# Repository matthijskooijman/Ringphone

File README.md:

Vintage phone audio player
==========================
This is the Ringphone project, a device that allows using old (mechanical
ring) phones to be used as a random audio player.

Repo status: Design is completely published, documentation is not
complete yet (mostly casing and firmware is lacking, harware is
documented well). Case design might not work as-is, but need some
changes to work with the latest boxes.py.

This project was created to facilitate the "Onze Kast" ("Our Cabinet")
project, which is a cabinet created by and for demented elderly people
with all kinds of things to explore and experience. In this cabinet,
there is an old bakelite phone that rings when someone approaches and
plays random audio samples when picked up. This repository documents the
design of this phone and contains all the needed source code and design
files to build it.

[More images...](./Images)

This project consists of three parts:
 - The electronics to connect to the telephone and detect motion.
 - The software to control everything.
 - A lasercut wooden case to house the electronics.

The sources and design files for these parts can be found in the `PCB`,
`RingPhoneSketch` and `Case` directories respectively. The `Data`
directory contains a template for the contents of the SD card.

A PDF version of the schematic, along with gerbers, board views and
other generated files for released board versions can be found under the
releases on the Github page.

This project uses an unmodified phone, connecting to it using the two
wires that normally connect to the telephone line (in essence, the
electronics emulate a telephone line). In theory it should be able to
work with any analog landline phone, though I have only tested it with
Dutch rotary dial phones from the sixties (and since the voltage and
current capability are not as high as true landlines, some phones might
not work).

Features
--------
Electronically, this project supports:
 - Making the phone ring.
 - Making the phone play a sound (through its regular earpiece).
 - Reading the rotary dial (this is supported electronically, but not by
   the software yet).
 - Detecting motion (using a standard motion detector module).

Receiving audio from the microphone is not supported at all.

The software supports:
 - Ringing the phone when motion is detected (with a fixed cooldown to
   not keep ringing all the time while motion is detected).
 - Playing a random sound whenever the phone is taken off-hook (also
   when it was not ringing).
 - Playing an "end of conversation" tone when the audio file completes
   playing.
 - Playing a new random sound whenever the rotary dial is used (this
   happens automatically, since using the rotary dial looks like putting
   the phone on-hook again).

Sketch
------
This sketch includes a copy of the
[AudioZero](https://github.com/arduino-libraries/AudioZero/) library,
modified to allow playing an audio file in the background. I considered
doing this properly (e.g. create a pull request for the library, maybe
use DMA for extra efficiency, etc.), but then it would probably be
better to add DAC out support to the
[ArduinoSound](https://github.com/arduino-libraries/ArduinoSound)
library instead (which was a bit more work than I was willing to invest
now).

Adding audio samples
--------------------
To add audio samples, they first must be encoded properly. The AudioZero
library is rather picky with the format and only understands 8-bit
unsigned 44.1kHz mono raw PCM files. This means the file just contains
the raw audio samples concatenated, without any header or other
accompanying information. Each sample is simply an 8-bit unsigned
integer. Note that this is even more raw than `.wav` file, which
typically have a header that describes the sample format in front of the
raw samples. This means that normal audioplayers cannot actually play
these raw PCM files, since they have no idea what format the samples are
in.

To encode these files, you can use Audacity. After loading a file, make
sure it is mono and has 44.1kHz sampling rate, then export it through
"File" -> "Export" -> "Export Audio..." and choose for "Other
uncompressed files" and then "Header: RAW (header-less)" and "Encoding:
Unsigned 8-bit PCM". Alternatively, you can convert to `.sou` files
using [this website](https://convertio.co/nl/sou-converter), but you
probably need to convert to 44.1Khz mono beforehand.

Once encoded, adding them is rather easy: Just dump the files onto the
μSD card. Make sure to use a `.raw` or `.sou` extension and to put the
files in the root (i.e. not in a subdirectory) of the μSD card.

Special sample file
-------------------
On the SD-card there should be a directory called `special` containing a
single file called `end.raw`. This is a sample (encoded as above), which
is played once after a normal sample has finished playing.

Electronics
-----------
Electronically a (Dutch) landline roughly works as follows:
 - A line consists of 2 connections, labeled "a" and "b" (which are
   interchangeable). There are some additional connections for extra
   bells and advanced features, but it seems those are often not used or
   even supported.
 - In idle, there is around 60V DC present on the line and little to no
   current flows (historically generated using lead-acid batteries, so
   48V is also common).
 - When ringing, a 100Vpp 25Hz AC voltage is superimposed on top of the
   DC voltage, which will make the bell ring.
 - When phone is on-hook, only a bell and capacitor (in series) are
   connected between the phone line a and b lines. The DC idle voltage
   is blocked by the capacitor and no current flows. The AC ringing
   voltage is passed by the capacitor and makes the bell ring. The
   frequency of the ringing signal directly controls the movement of the
   bell hammer and thus the sound.
 - When the horn is lifted, the bell is removed from the line and a
   microphone and speaker are connected to the line (along with a
   transformer and other supporting components). When this happens, the
   DC resistance of the phone drops, more DC current (about 50mA) flows
   (through the speaker and microphone) and the line voltage drops (to
   something like 15VDC). This extra current can be detected by the
   phone central (originally by a relay coil connected in series that
   would switch when the current was high enough), to initiate a
   connection.
 - All of this is operated using balanced signals, meaning that the
   impedance / resistance of both lines is the same (as opposed to
   single-ended, where one line is grounded and the other carries the
   signal). This balanced impedance causes any noise to be picked up by
   both lines equally and allows the receiving end to cancel out the
   noise against itself, which is especially important when phone lines
   get longer and wired close together.

This same system is used pretty much everywhere, though some details and
voltage might differ from country to country.

I have found [a very good article][telefoonlijn] that describes this (in
Dutch, but the illustrations should be insightful even when you do not
speak Dutch).

Here's some other documentation about telephones and telephone lines:
 - [Telephone line audio interface circuits](http://www.epanorama.net/circuits/teleinterface.html)
 - [Telephone ringing circuits](http://www.epanorama.net/circuits/telephone_ringer.html)
 - [electrical characteristics of telephone lines](https://computer.rip/2023-05-07-electrical-characteristics-of-telephone-lines.html)

Playing sound
-------------
Initial experiments show that playing sound over a telephone from an
Arduino is easy: Just connect one wire to ground and the other to a PWM
pin and call the Arduino `tone()` function. This makes the phone beep at
a single frequency and can play simple monotonic melodies.

To actually play (recorded) audio, connect it to a true analog output
(DAC) pin, such as the `A0` pin on M0 boards (I used the Adafruit
Feather M0 Adalogger, since it is compact and has an SD-card
integrated).

Some observations:
 - Since we connect one end to the Arduino GND, this is not a proper
   balanced output. Since cables are short and the phone itself is not
   grounded (so no possibility for a ground loop), this does not seem
   like a problem.
 - The current capability of microcontroller output pins is limited
   (often just a few mA for more modern ARM-based microcontrollers), so
   connecting a speaker directly might overload pins. The telephone
   speaker is fairly low power, though (meaning it has a higher
   impedance, so less current flows at a given voltage), so this might
   be within limits. A line nominally has 600Ω of impedance at audio
   frequencies, leading to 5V / 600Ω = 8mA which is acceptable for an
   Arduino Uno. With my phone, the DC resistance was about 300Ω, so take
   that into account when you leave a constant voltage on the phone.
 - The output voltage of the Arduino is higher than normal signal
   voltage for a telephone line. A typical telephone line supplies about
   15VDC when off-hook, but only the AC (audio) signal that is on top of
   that DC voltage reaches the speaker (through a transformer). This
   audio signal is typically -9dBm, which corresponds to 275mVRMS, or
   778mVpp. Apparently this is where the term "line level" comes from,
   which defines 0dBm as 1mW into a 600Ω impedance), so the 3.3V or 5V
   of a typical Arduino will result in a louder audio signal. I suspect
   these voltages are not high enough to cause problems, though.
 - When in doubt, adding some output impedance (e.g. a series resistor
   of, a couple of hundred ohms) could both limit the voltage
   transferred to the speaker and current drawn from the Arduino.

Making the phone ring
---------------------
To make the phone ring, we need a higher voltage and current (the 3.3V
or 5V of the microcontroller pins is not sufficient to let the bell
coils generate enough magnetic force to ring). The official voltage is
100V peak-to-peak (so switching between a +50V and -50V difference
between a and b), on top of any DC voltage already present.

Fortunately for us, a typical old-skool phone can already ring with a
lot lower voltages, though the volume might be a bit lower (though for
my purposes it was more than loud enough). It does depend on the phone:
One of mine started ringing at 24Vpp, where another needed 52Vpp.

Connecting an AC voltage directly to the phone's wires makes it ring. I
used an AC power supply I had lying around that provided something like
20 or 30VAC (RMS).

For the final build, I did not want to use an AC power supply, but
resort to just a single DC power supply for the entire project. So to
generate an AC signal, I tried a H-bridge. A H-bridge is a
configuration of four transistors connected to two wires in such a way
that both wires can independently be set to a high or low level. These
are typically used to run electrical motors in two directions,  but they
also work fine to generate an AC voltage. As added bonus, by switching
*both* lines in a mirrored way, you effectively double the voltage (so
30VDC switches between -30V to 30V (between a and b), so 60Vpp. This
does not result in a nice and clean sine wave, but since we are only
trying to energize a coil to make a hammer bang into a bell, a rough
square wave is just as fine.

To generate the higher DC voltage, I used a step-up power supply module.
The entire project is fed using a standard 5V USB power supply, and this
step-up module generates the (around 30VDC IIRC) Vdrive used to ring the
phone and generate a 15V idle voltage.

Also interesting is that the ring current only lasts for a few ms, which
is enough to charge the DC-blocking capacitor inside the phone, after
which the ring current drops to zero. This is probably intentional, to
generate a short pulse of force to move the hammer against the bell, but
allowing it to bounce off again to get a clean sound.

[telefoonlijn]: https://verstraten-elektronica.blogspot.com/p/plain-old-telephone-service.html

Combining sound and ringing
---------------------------
I tried a few things to properly combine these into a single phone line
signal, but ended up using an opamp for the DC idle voltage and
superimposed audio signal, a H-bridge for the ring signal using a diode
and capacitor to combine both signals onto the phone line.

The opamp (U1A) uses a "virtual ground" of half VDrive on its positive
input terminal. This means that in idle, when no audio signal is output
(*i.e.* the DAC output is fixed), the opamp output equals this virtual
ground (or 15VDC). Capacitor C1 is charged by the opamp, so it blocks
any DC current and voltage from flowing back into the microcontroller,
while at the same time providing a 15V offset to the microcontroller DAC
output.

When the microcontroller starts playing sound, the opamp starts
amplifying this superimposed on the 15V idle voltage. This happens
because the audio signal changes too fast for C1 to keep up, so the
opamp negative input terminal is the audio signal plus the 15V over C1.
The opamp feedback resistors (R1/RV1) determine the amount of
amplification and were chosen to provide at most 10× amplification.

When not ringing, the H-bridge is configured with both sides pulling
down. Then when on-hook, no current flows so terminal b is at 0V,
terminal a at 15V (provided by the opamp), and C3 is charged to 15V.
This results in a 15VDC idle voltage on the phone. When the phone is
taken off-hook, a current starts to flow and the idle voltage drops
(because of the output resistors R4 and R6). When audio plays, the
(amplified) audio signal is superimposed on top of this idle voltage.

When ringing, the outputs of the H-bridge alternate between high/low and
low/high, creating two 30Vpp (relative to GND) square waves on each
terminal. Since these square waves are inverted, they result in an
effective 60Vpp square wave over the two terminals. Because C3 stays
(mostly) charged during the ring, this ring voltage is superimposed over
the 15VDC idle voltage. Diode `D1` ensures that these higher voltages
are blocked from the opamp output.

TODO: Scope image?

Output levels & impedance
-------------------------
The opamp provides at most 10× amplification. With 0-1V DAC output, this
results in 0-10V audio output (+/-5V, or 10Vpp or 3.5VRMS or +8dBm).
This seems like much given the nominal -9dBm that is documented, but
this was what I needed to get a sufficiently loud output signal. This
level is calculated at the opamp output, so the level will be lower at
the a terminal because of the voltage drop over R4. This drop is caused
by current flowing into the phone, but also through R5 into the H-bridge
(which already halves the voltage, by forming a 1:1 divider between R4
and R5).

Note that the audio signal is only present on terminal a, while terminal
b stays at a fixed voltage (except for some small variations due to
current changes). Real phone lines usually have the a mirrored signal on
the other terminal, but this is not require for proper balancing (only
the output impedance is relevant).

With short cable lengths this balancing did not seem to make a lot of
difference, but when adding 50m of cable, shorting R6 would introduce
significant audible noise, which was gone with R6 restored.

In hindsight, the output impedance is probably not completely balanced,
since there are two drivers of each 470Ω on the a terminal (the opamp
and the H-bridge), so the effective output impedance is probably only
half of that. Doubling R4 and R5 might help, though I did not try that.
Note that C3 blocks DC current, so the DC output impedance of terminal a
is not influenced by the H-bridge, but higher frequency signals (e.g.
noise) are passed by C3.

I have considered disabling the H-bridge on the a-terminal when not
ringing, rather than driving it low. This would prevent current from
flowing into the H-bridge and halving the audio output voltage and would
probably improve the output balancing. However, this would also prevent
C3 from staying charged at 15V, reducing the ring voltage.

In hindsight, keeping the H-bridge enabled when on-hook and disabled
when off-hook and playing audio might have been a good compromise. That
means it needs a little bit of time (RC=470Ω×33μF = 15ms) to charge C3
after having been off-hook, but that should not be a problem, I expect.
To implement this, PCB changes are needed to use two different H-bridges
(already present in the chip used) for the a and b terminals. Doing so
allows disabling the one on the a terminal, while keeping the one on the
b terminal enabled.

Off-hook detection
------------------
When the phone is taken off-hook, the DC resistance of the phone drops
and the current increases. To detect this, R6 is used as a shunt
resistor. When idle, the left side of the resistor (connected to the
H-bridge) is at (about) 0V, so by measuring the right side of the
resistor (at terminal b), we can measure the voltage drop over the
resistor (which is linear with the current).

Since terminal b can go up to 30V when ringing, it cannot be measured
directly (the MCU does not like such voltages). Instead, a 1:11 resistor
divider is used to bring the voltage down to acceptable levels. To
prevent loading the terminal (and changing the output impedance) with
this divider, a unity gain amplifier is inserted (using the second opamp
channel in the chip that was already used for the audio output).

To detect off-hook, a voltage measurement is made (using the
microcontroller ADC) and compared with a threshold. When the phone is
ringing, the voltage and thus the current is higher, so the threshold is
also higher.

When the phone rings, terminal b will be high half of the time. In this
case, the left side of R6 will be at something like 30V and the (now
negative) current through R6 will put the measured voltage below 30V. It
turned out to be tricky to properly apply a threshold here (which is
heavily influenced by the power supply level). To make things easier,
while ringing, the code simply only checks for hook status when terminal
b is low (a little bit afte making it low, since then the current is
highest and easiest to detect).

I have also experimented with some circuits to filter out the ring
current completely, leaving only the DC current, but I could not make
that reliably (a fundamental problem is that if you want to filter out
a 25Hz signal, the filter needs quite some periods to detect a change in
DC level). The current approach with measuring the current at strategic
moments is able to detect off-hook within on period (40ms).

Note that these thresholds have been determined experimentally and are
probably tuned to the phone used. When using a different phone, the
currents might be different and the thresholds might need to be tweaked.

License
-------
The sketch is licensed under the MIT license. The included AudioZero
library (including my modifications) is dual-licensed under the GNU GPL
and LGPL licenses. See the individual source files for more details.

The PCB and case designs are Open Hardware and are licensed under the
CERN-OHL-P v2 or any later version. See the README.md in both
subdirectories for details.

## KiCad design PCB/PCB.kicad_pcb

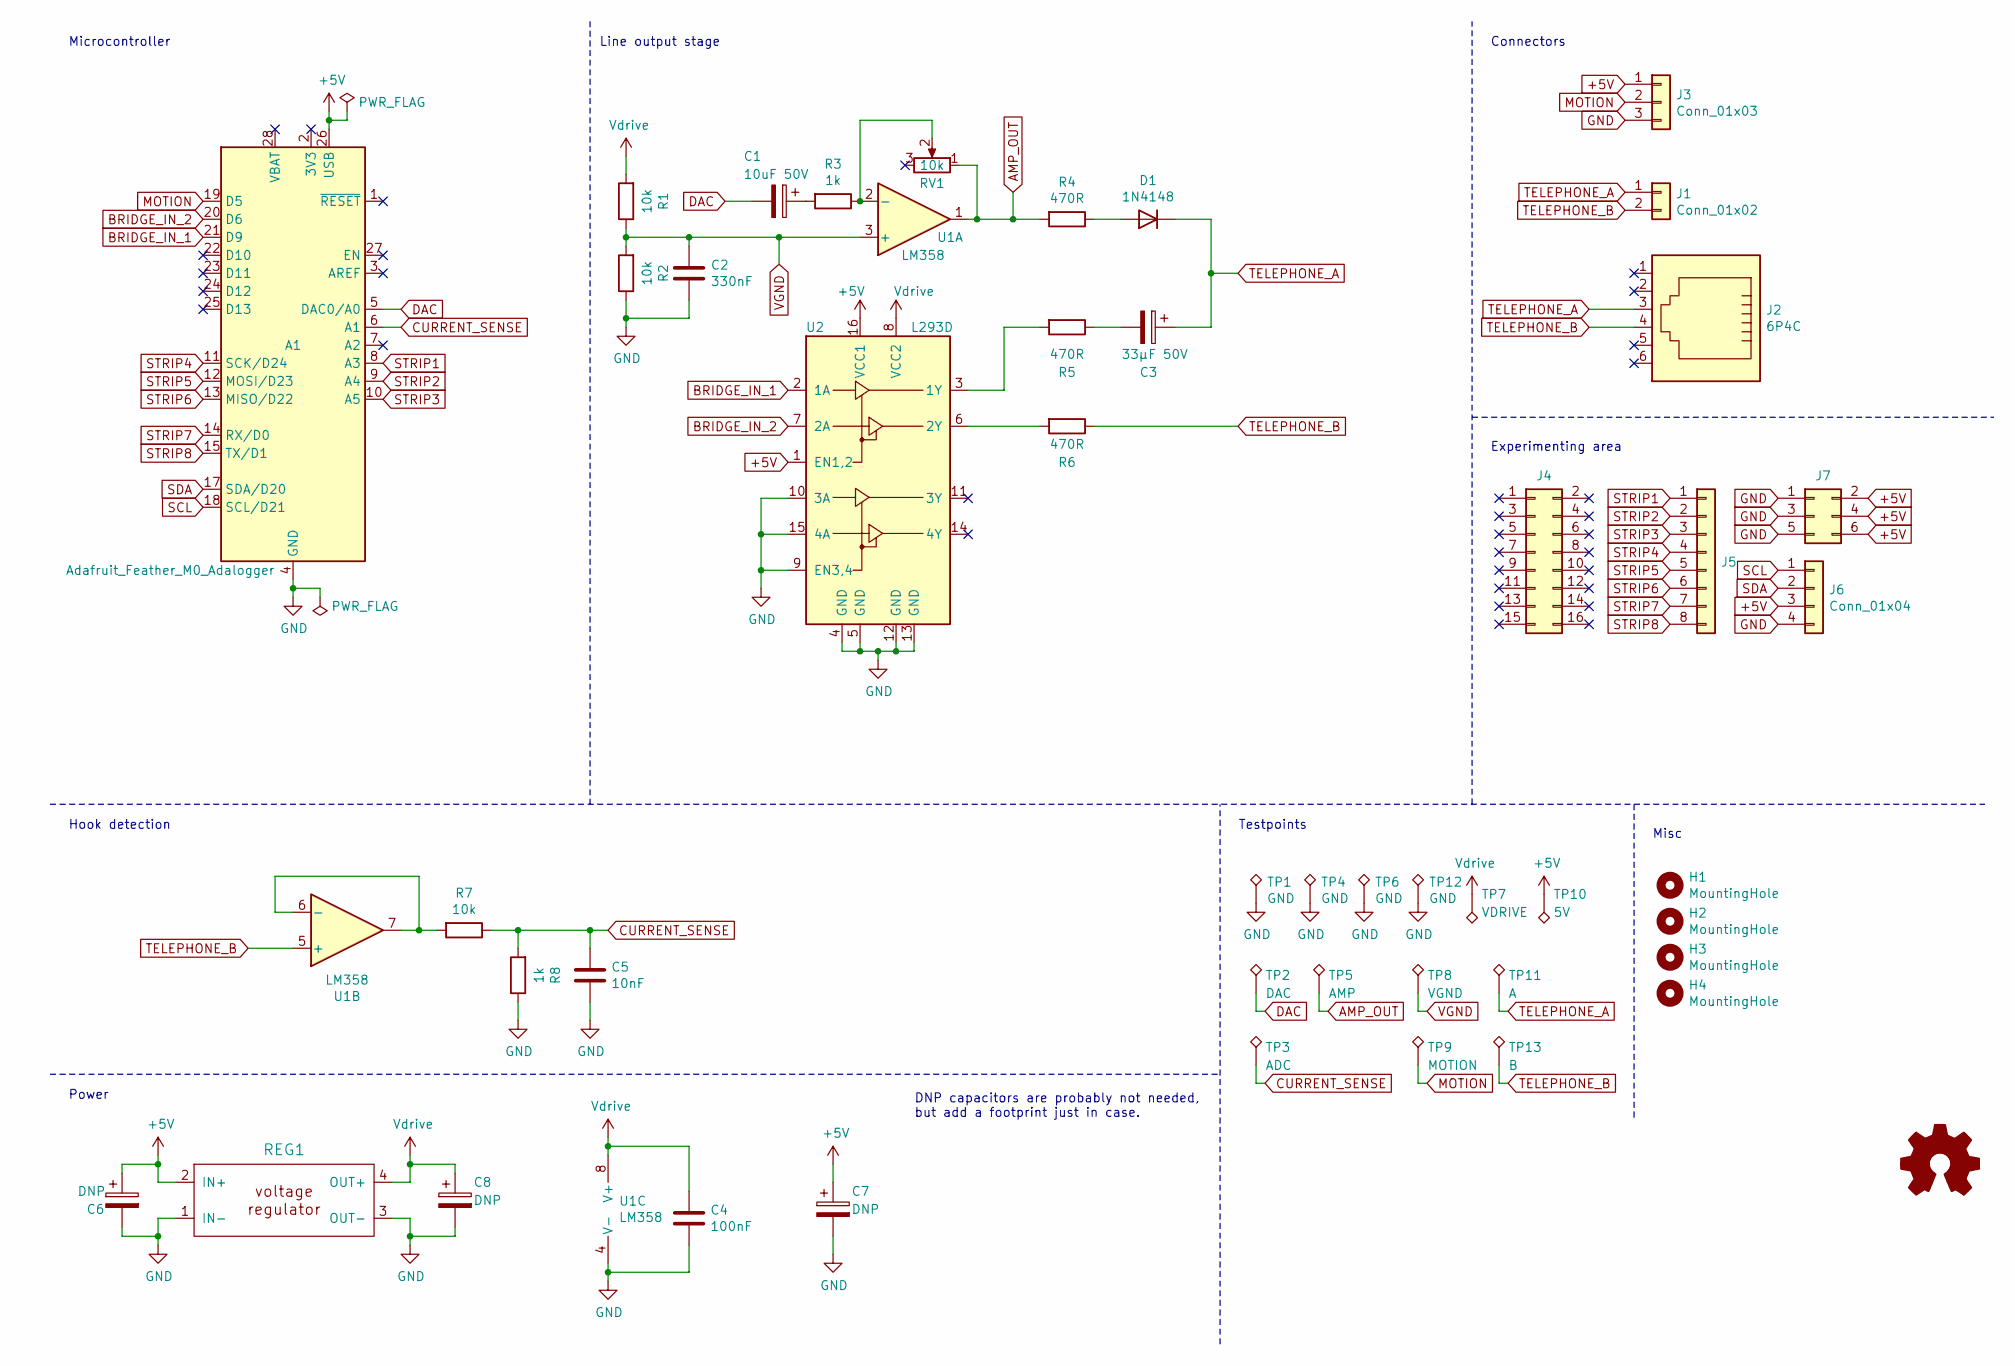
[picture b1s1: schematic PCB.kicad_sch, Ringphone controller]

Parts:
A1: Adafruit_Feather_M0_Adalogger; Adafruit_Feather
C1: 10uF 50V; CP_Radial_D5.0mm_P2.00mm
C2: 330nF; C_Disc_D7.0mm_W2.5mm_P5.00mm
C3: 33μF 50V; CP_Radial_D5.0mm_P2.00mm
C4: 100nF; C_Disc_D7.0mm_W2.5mm_P5.00mm
C5: 10nF; C_Disc_D7.0mm_W2.5mm_P5.00mm
C6, C7, C8: DNP; CP_Radial_D5.0mm_P2.00mm
D1: 1N4148; D_DO-35_SOD27_P7.62mm_Horizontal
H1, H2, H3, H4: MountingHole; MountingHole_2.7mm_M2.5
J1: Conn_01x02; PinHeader_1x02_P2.54mm_Vertical
J2: 6P4C; RJ12_Amphenol_54601-x06_Horizontal
J3: Conn_01x03; PinHeader_1x03_P2.54mm_Vertical
J4: Conn_02x08_Odd_Even; PinHeader_2x08_P2.54mm_Vertical
J5: Conn_01x08; PinHeader_1x08_P2.54mm_Vertical
J6: Conn_01x04; PinHeader_1x04_P2.54mm_Vertical
J7: Conn_02x03_Odd_Even; PinHeader_2x03_P2.54mm_Vertical
LOGO1: Logo_Open_Hardware_Small; OSHW-Logo2_7.3x6mm_SilkScreen
R1, R2, R7: 10k; R_Axial_DIN0207_L6.3mm_D2.5mm_P7.62mm_Horizontal
R3, R8: 1k; R_Axial_DIN0207_L6.3mm_D2.5mm_P7.62mm_Horizontal
R4, R5, R6: 470R; R_Axial_DIN0207_L6.3mm_D2.5mm_P7.62mm_Horizontal
REG1: REGULATOR_MODULE; MT3608
RV1: 10k; Potentiometer_Piher_PC-16_Single_Horizontal
TP1, TP4, TP6, TP12: GND; TestPoint_THTPad_2.0x2.0mm_Drill1.0mm
TP2: DAC; TestPoint_THTPad_2.0x2.0mm_Drill1.0mm
TP3: ADC; TestPoint_THTPad_2.0x2.0mm_Drill1.0mm
TP5: AMP; TestPoint_THTPad_2.0x2.0mm_Drill1.0mm
TP7: VDRIVE; TestPoint_THTPad_2.0x2.0mm_Drill1.0mm
TP8: VGND; TestPoint_THTPad_2.0x2.0mm_Drill1.0mm
TP9: MOTION; TestPoint_THTPad_2.0x2.0mm_Drill1.0mm
TP10: 5V; TestPoint_THTPad_2.0x2.0mm_Drill1.0mm
TP11: A; TestPoint_THTPad_2.0x2.0mm_Drill1.0mm
TP13: B; TestPoint_THTPad_2.0x2.0mm_Drill1.0mm
U1: LM358; DIP-8_W7.62mm_Socket_LongPads
U2: L293D; DIP-16_W7.62mm

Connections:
+5V: A1.26 (USB), C6.1, C7.1, J3.1, J6.3, J7.2, J7.4, J7.6, REG1.2 (IN+), TP10.1, U2.1 (EN1,2), U2.16 (VCC1)
AMP_OUT: R4.2, RV1.1, TP5.1, U1.1
BRIDGE_IN_1: A1.21 (D9), U2.2 (1A)
BRIDGE_IN_2: A1.20 (D6), U2.7 (2A)
CURRENT_SENSE: A1.6 (A1), C5.1, R7.1, R8.2, TP3.1
DAC: A1.5 (DAC0/A0), C1.2, TP2.1
GND: A1.4 (GND), A1.16 (GND), C2.2, C4.2, C5.2, C6.2, C7.2, C8.2, J3.3, J6.4, J7.1, J7.3, J7.5, R2.1, R8.1, REG1.1 (IN-), REG1.3 (OUT-), TP1.1, TP4.1, TP6.1, TP12.1, U1.4 (V-), U2.4 (GND), U2.5 (GND), U2.9 (EN3,4), U2.10 (3A), U2.12 (GND), U2.13 (GND), U2.15 (4A)
MOTION: A1.19 (D5), J3.2, TP9.1
unnamed: C1.1, R3.2
unnamed: C3.2, R5.1
unnamed: D1.2 (A), R4.1
unnamed: R3.1, RV1.2, U1.2 (-)
unnamed: R7.2, U1.6 (-), U1.7
unnamed: R5.2, U2.3 (1Y)
unnamed: R6.2, U2.6 (2Y)
SCL: A1.18 (SCL/D21), J6.1
SDA: A1.17 (SDA/D20), J6.2
STRIP1: A1.8 (A3), J5.1
STRIP2: A1.9 (A4), J5.2
STRIP3: A1.10 (A5), J5.3
STRIP4: A1.11 (SCK/D24), J5.4
STRIP5: A1.12 (MOSI/D23), J5.5
STRIP6: A1.13 (MISO/D22), J5.6
STRIP7: A1.14 (RX/D0), J5.7
STRIP8: A1.15 (TX/D1), J5.8
TELEPHONE_A: C3.1, D1.1 (K), J1.1, J2.3, TP11.1
TELEPHONE_B: J1.2, J2.4, R6.1, TP13.1, U1.5 (+)
VGND: C2.1, R1.1, R2.2, TP8.1, U1.3 (+)
Vdrive: C4.1, C8.1, R1.2, REG1.4 (OUT+), TP7.1, U1.8 (V+), U2.8 (VCC2)

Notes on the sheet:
Misc
Testpoints
Power
Hook detection
Line output stage
Microcontroller
Experimenting area
DNP capacitors are probably not needed, but add a footprint just in case.
Connectors

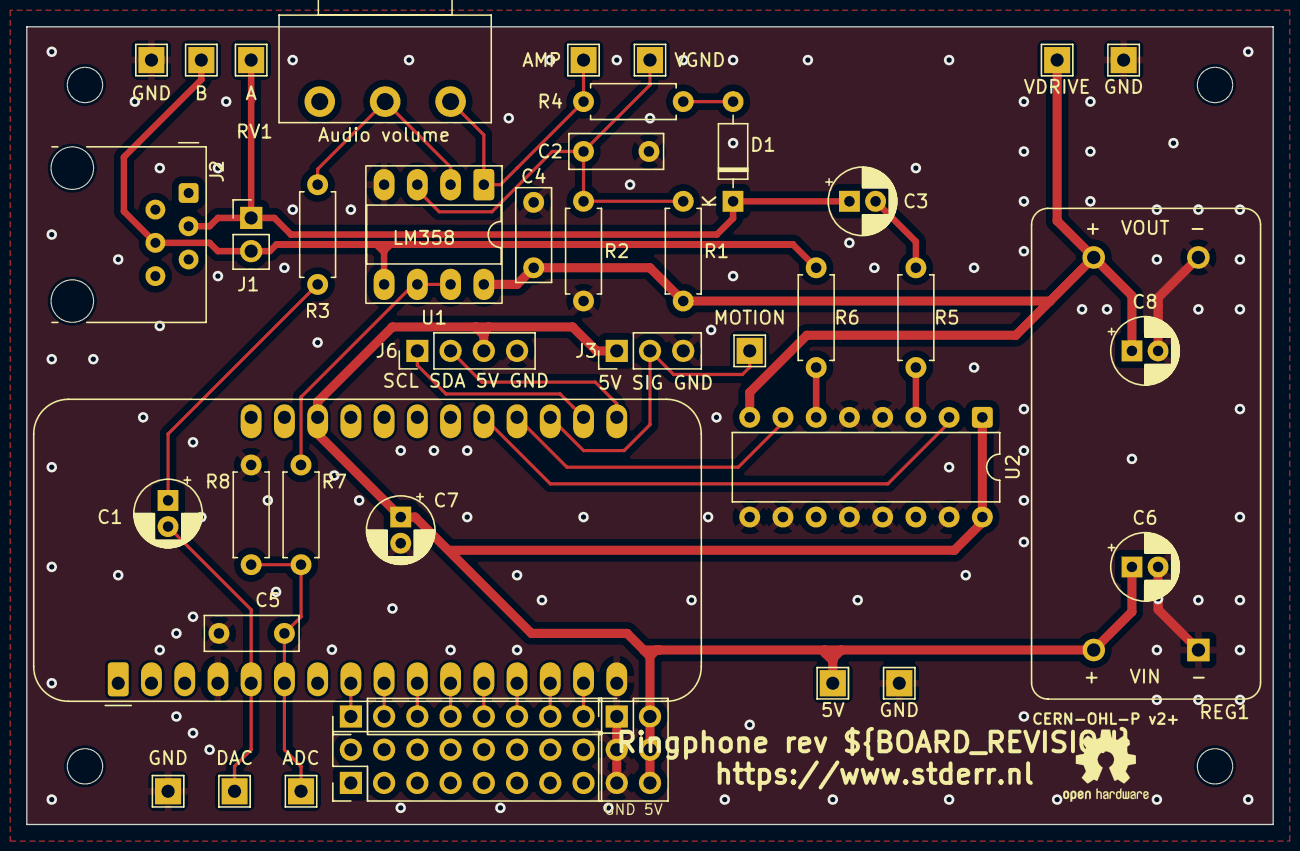
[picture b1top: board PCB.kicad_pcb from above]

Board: 2 copper layers, 95.2 x 61.0 mm, 47 parts (0 on the bottom side), 29 nets.

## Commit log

2019-06-15 Add AudioZero code
    This adds the library code as-is, from commit
    5a60840 at https://github.com/arduino-libraries/AudioZero. Adding the
    library here rather than using the original makes it easier to make some
    quick modifications.
2019-06-15 Allow playing in the background
    Additionally, make sure that playback actually stops at the end of the
    file, rather than replaying the last buffer over and over. This enables
    the timer interrupt right away at begin, rather than waiting for the
    first play().
2019-06-15 Sketch: Add complete logic
    This is a first version of the sketch that should completely implement
    the logic. It also adds support for a motion detector to trigger the
    ringing.
2019-06-15 Add initial sketch
    This version just rings when the phone is on-hook and repeatedly plays
    an audio file when the phone is of-hook.
2019-06-15 Sketch: Modify scope trigger helper stuff
2019-06-15 Sketch: Set motion detector pin mode
2019-06-15 Sketch: Tweak hook detection
    It seems it would sometimes trigger too soon in idle, so the threshold
    is increased (probably due to noise, adding a capacitor also seemed to
    have helped). Also, after ringing, leave some extra time for the current
    to stabilize again.
2019-06-16 Sketch: Play a random file from the SD card
2019-06-16 Sketch: Never play the same file as the previous 5
2019-06-16 Sketch: Add (disabled) hook detection debug code
2019-06-16 Sketch: Always play sound when phone is taken offhook
    This now happens even when waiting for motion or during cooldown.
2019-06-16 Sketch: Reduce ring frequency to 25Hz
    This is the regular frequency used on telephone lines.
2019-06-19 Add PCB design v1
2019-06-25 Improve fab markings for printing
    It seems a lot of stuff in the file was reordered or otherwise modified,
    probably due to a newer kicad nightly version.
2019-06-27 Sketch: Update pinout to PCB v1
2019-06-27 Sketch: Improve led feedback
    This used the green led to signal off-hook rather than the red one, and
    blinks the red led in case of startup errors.
2025-04-17 Add case
    This is probably not the final version, I still have some local changes
    that might need to be incorporated. This version also does not work with
    the latest boxes.py, needs some changes for that.
2025-04-17 Add initial README
    This still has some TODOs and lacks info on the case and firmware, but
    it already documents the hardware quite well.
2025-04-18 README: Add photos
2025-04-18 RingPhoneSketch: Add license
2025-04-18 RingPhoneSketch: Set cooldown time to the final 300 seconds
    It was still set to the 10s for testing.
2025-04-18 RingPhoneSketch: Switch off the red LED at boot
2025-04-18 PCB: Convert to KiCad 9
    This is the result of opening the design in KiCad 9, going through the
    schematic and board setup dialogs and saving again. This updates to new
    file extensions and severely changes the internal file contents, but
    should not modify the design in any way.
    This also removes the PCB-cache.lib file, since it is no longer needed
    since KiCad 6.
2025-04-18 PCB: Update all symbols from library
2025-04-18 PCB: Update Feather symbol and footprint
    This changes from a locally created one to the KiCad library version of
    it (which has seen some changes before it was merged).
    This also seems to completely rewrite the .kicad_pcb file, so maybe the
    earlier conversion to KiCad9 did not work (or was not committed), so
    the diff of this commit on the PCB is useless.
2025-04-18 PCB: Update all footprints from library
2025-04-18 PCB: Reattach vias to GND
    Somewhere in the KiCad upgrade, it seems some vias got attached to
    different nets. This manually fixes them.
2025-04-18 PCB: Fix DRC errors
    This updates a footprint, makes small layout changes and ignores some
    violations.
2025-04-18 PCB: Improve DRC rules
    This unignores some rules, and adds some custom rules to ignore some
    expecte violations.
2025-04-18 PCB: Update some symbol references
    These were renamed in the KiCad libraries.
2025-04-18 Setup PCB-workflows automation
2025-04-18 Release PCB version 1.1
2025-04-18 Update license info, switch to CERN-OHL-P v2
    This also puts the licens on the silkscreen.
2025-04-18 README: Point to releases for a schematic PDF

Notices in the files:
README.md:
License:
The sketch is licensed under the MIT license. The included AudioZero
library (including my modifications) is dual-licensed under the GNU GPL
and LGPL licenses. See the individual source files for more details.
The PCB and case designs are Open Hardware and are licensed under the
CERN-OHL-P v2 or any later version. See the README.md in both
subdirectories for details.
PCB/PCB.kicad_pcb:
CERN Open Hardware Licence v2 - Permissive
